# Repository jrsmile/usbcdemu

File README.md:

usbcdemu
========

USB CD-ROM Emulator

more Information can be found here: http://www.renosite.com/forum/viewforum.php?f=7

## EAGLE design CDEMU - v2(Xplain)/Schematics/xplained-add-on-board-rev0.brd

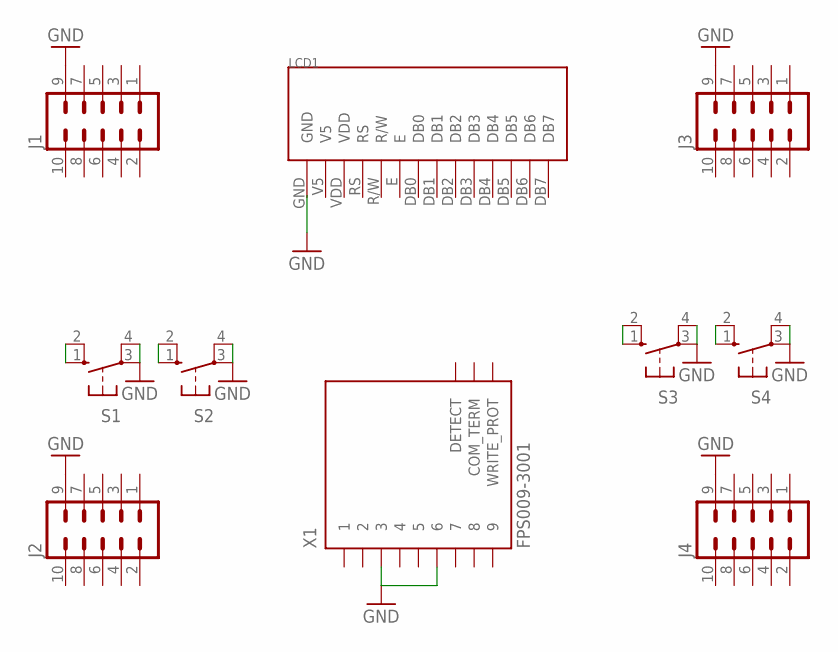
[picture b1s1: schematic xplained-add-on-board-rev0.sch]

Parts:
J1, J2, J3, J4: ML10
LCD1: NHD-C0220AA-FSW-FTW
S1, S2, S3, S4: 10-XX; B3F-10XX
X1: FPS009-3001; FPS009-3000

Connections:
GND: J1.9, J2.9, J3.9, J4.9, S1.3, S1.4 (P1), S2.3, S2.4 (P1), S3.3, S3.4 (P1), S4.3, S4.4 (P1), X1.3, X1.6
unnamed: S1.1 (S), S1.2 (S1)
unnamed: S2.1 (S), S2.2 (S1)
unnamed: S3.1 (S), S3.2 (S1)
unnamed: S4.1 (S), S4.2 (S1)

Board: 2 copper layers, 10 parts (4 on the bottom side), 5 nets, no tracks yet.

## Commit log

2013-02-20 initial commit from sourceforge
2013-02-20 Update README.md
    added forum Link
